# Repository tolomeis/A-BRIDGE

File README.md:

View this project on [CADLAB.io](https://cadlab.io/project/1067). 

# A-BRIDGE
Source files for the A-BRIDGE motor driver board

The A-Bridge is a small dual H-BRIDGE based on the integrated DMOS full-bridge A4950, capable to run 2 motors with a continuos current of 3A (3.5 with a heat dissipator) and a peak current of 5A. The bridge operates in PWM LAP, so, compared to the typical PWM SM control, you have less resolution but a more precise control of the speed. The inverted PWM signal required for LAP control is generated internally with a 74HC240 tri-state inverter, that also gives you the possibility to disable the bridge and the motor using the Enable input.

FEATURES:
 + Control 2 brushed DC motors
 + Input voltage: 8-40V
 + Output current: 3A continuos, 3.5 with heat dissipator, 5A peak
 + Overcurrent  short circuit protection
 + Enable input to disable the bridge

WARNING:
Some motor manifacturers (e.g. micromotors) use capacitors to reduce spikes and noise, it's recommended not to use that type of motors with this bridge. Check the motor's specification to know if your motor has the capacitors.
 
---

How to use

Basically this is a H Bridge, the only difference between this and the other typical commercial bridges is the integrated LAP control, this mean that you can control both speed and direction using the same signal. In particular:

|PWM duty cycle  |Motor speed|
|----------------|-----------|
|0%              |Full Backwards|
|50%             |Brake      |
|100%            | Full Forwards|

The ENABLE pin is used to disable the bridge. When LOW the bridge is operating at normal condition, when HIGH the bridge will enter in low power standby mode after 1ms. This is useful because the *brake* condition, with duty cycle 50%, does not means that the motor is turned off, but means that the motor is **braked, and it will draw current to remain still**. This is the worst efficience condition for the bridge, then, unless with small motor, it will heat up very fast. I recommend you not to remain in *brake* conditon for more than a half a minute. Therefore, for simply stop the motor you can set duty cicle to 50% and then disable the bridge with EN pin.

------

The circuit is very simple, basically it consist of two A4950, the 74HC240 and 5 bulk capacitors.

The A4950 can also provide a current feedback, but the  sensing resistor also triggers the automatic current limiting system of the IC, that decrease the maximum output current. For example, a 0.25ohm resistor would limit the maximum current to 2A. This is the reason why i choose not to use the current sensing in this version of the board. If you want the current sensing feature you can use a external ammeter IC or consider the powerful [uBridge by Officine Robotiche](https://github.com/officinerobotiche/uBridgePCB).

----

###TESTING

Every bridge is tested with various conditions of load. The tests measures voltage drop, voltage overshoot, rise time and temperature.
Here you can see differents measures obtained with 2 different motors: a micromotors 12V 300mA geared motor and a lawnmower motor, running at 20V and absorbing 600mA with no load. You can see that with the lawnmower robot motor the voltage overshoot is really high, this happens mainly because the Arduino (which i used in this tests) produces the PWM signal with a too low frequency, 1Khz or 5Khz depending by the pin. To use big motors i recommend to use a frequency PWM at least of 10-15Khz, for example by using the [setPwmFrequency](http://playground.arduino.cc/Code/PwmFrequency) function on Arduino or by using another microcontroller (e.g. ARM or PIC)

###Micromotors motor:

###Lawnmower motror:

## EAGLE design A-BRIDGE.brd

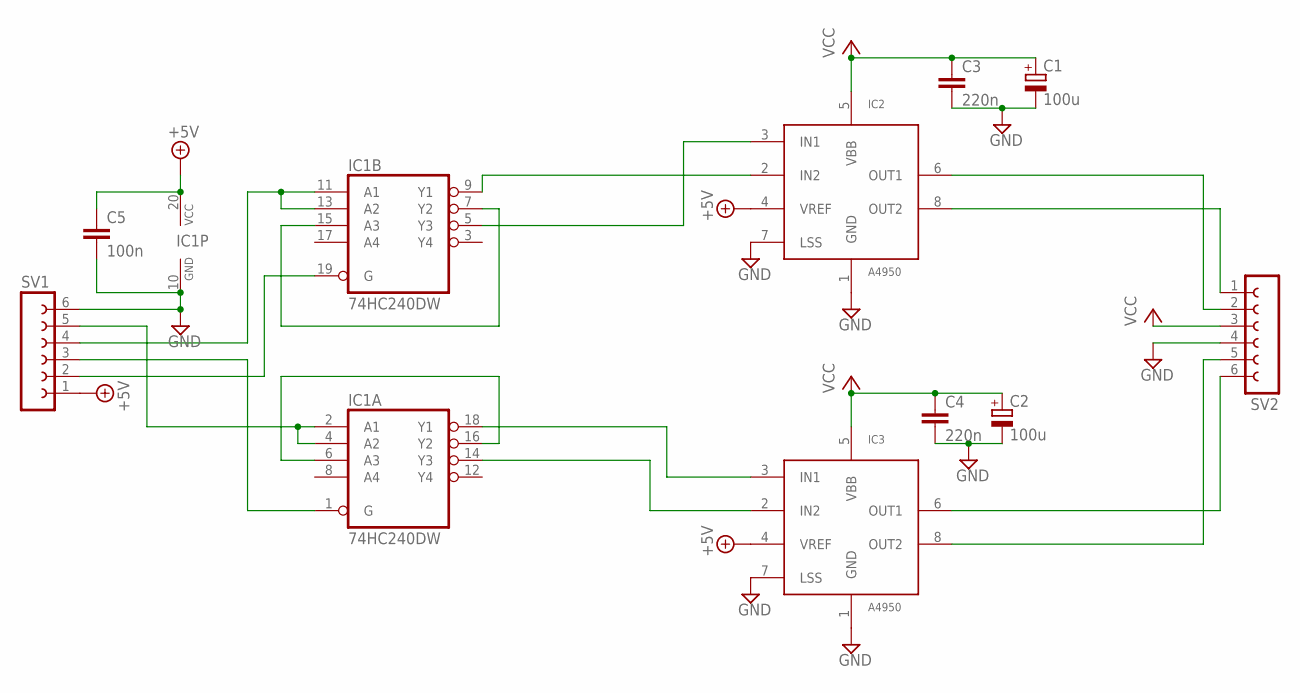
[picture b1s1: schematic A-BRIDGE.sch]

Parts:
C1, C2: 100u; UD-6,3X7,7_NICHICON_HS
C3, C4: 220n; C0805K
C5: 100n; C1206K
IC1: 74HC240DW; SO20W
IC2, IC3: A4950; SOICN-8
SV1, SV2: FE06-1; FE06

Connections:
+5V: C5.1, IC1.20 (VCC), IC2.4 (VREF), IC3.4 (VREF), SV1.1
GND: C1.-, C2.-, C3.2, C4.2, C5.2, IC1.10 (GND), IC2.1 (GND), IC2.7 (LSS), IC3.1 (GND), IC3.7 (LSS), SV1.6, SV2.4
unnamed: IC2.6 (OUT1), SV2.2
unnamed: IC2.8 (OUT2), SV2.1
unnamed: IC3.6 (OUT1), SV2.6
unnamed: IC3.8 (OUT2), SV2.5
unnamed: IC1.14 (Y3), IC3.2 (IN2)
unnamed: IC1.18 (Y1), IC3.3 (IN1)
unnamed: IC1.6 (A3), IC1.16 (Y2)
unnamed: IC1.2 (A1), IC1.4 (A2), SV1.5
unnamed: IC1.11 (A1), IC1.13 (A2), SV1.4
unnamed: IC1.7 (Y2), IC1.15 (A3)
unnamed: IC1.9 (Y1), IC2.2 (IN2)
unnamed: IC1.5 (Y3), IC2.3 (IN1)
unnamed: IC1.1 (G), SV1.3
unnamed: IC1.19 (G), SV1.2
VCC: C1.+, C2.+, C3.1, C4.1, IC2.5 (VBB), IC3.5 (VBB), SV2.3

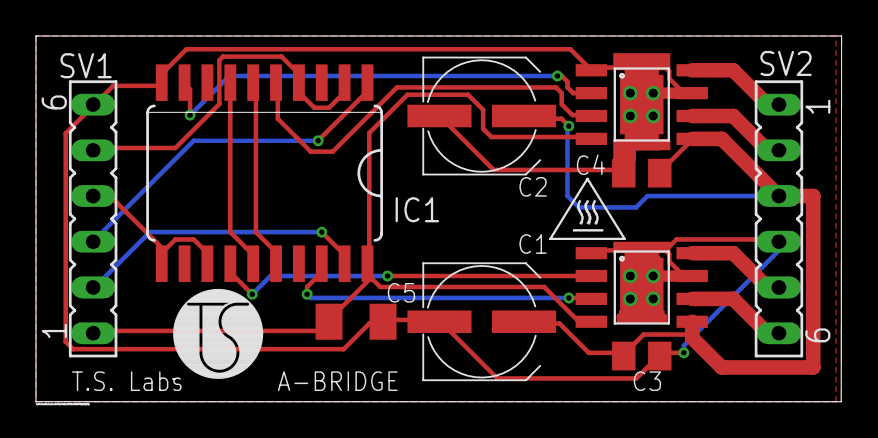
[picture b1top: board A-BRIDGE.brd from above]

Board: 2 copper layers, 44.8 x 20.3 mm, 10 parts (0 on the bottom side), 17 nets.

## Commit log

2016-06-18 :boom::camel: Added .gitattributes & .gitignore files
2016-06-18 Added first files
2016-06-18 Added datasheet
2016-06-19 Added photo
2016-06-19 Added resources
2016-06-19 Added pinout
2016-06-22 Updated Pinout
2016-06-28 Added test screen
2016-06-28 Added tests screen
2016-09-24 A-BRIDGE rev.2
    Added silkscreen pinout
    Fixed grounding problems
    Better Heat dissipation
2016-12-20 rev2.01
    Added "hot surface" warning
    Better heat dissipation on bottom area
    Bigger capacitor's footprint for hand soldering
2018-05-21 Backlink to CADLAB.io has been added.
2019-02-25 Deleted old pinout

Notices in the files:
A-BRIDGE.brd:
Design by Simone Tolomei - T.S. Labs - CC-BY-SA
